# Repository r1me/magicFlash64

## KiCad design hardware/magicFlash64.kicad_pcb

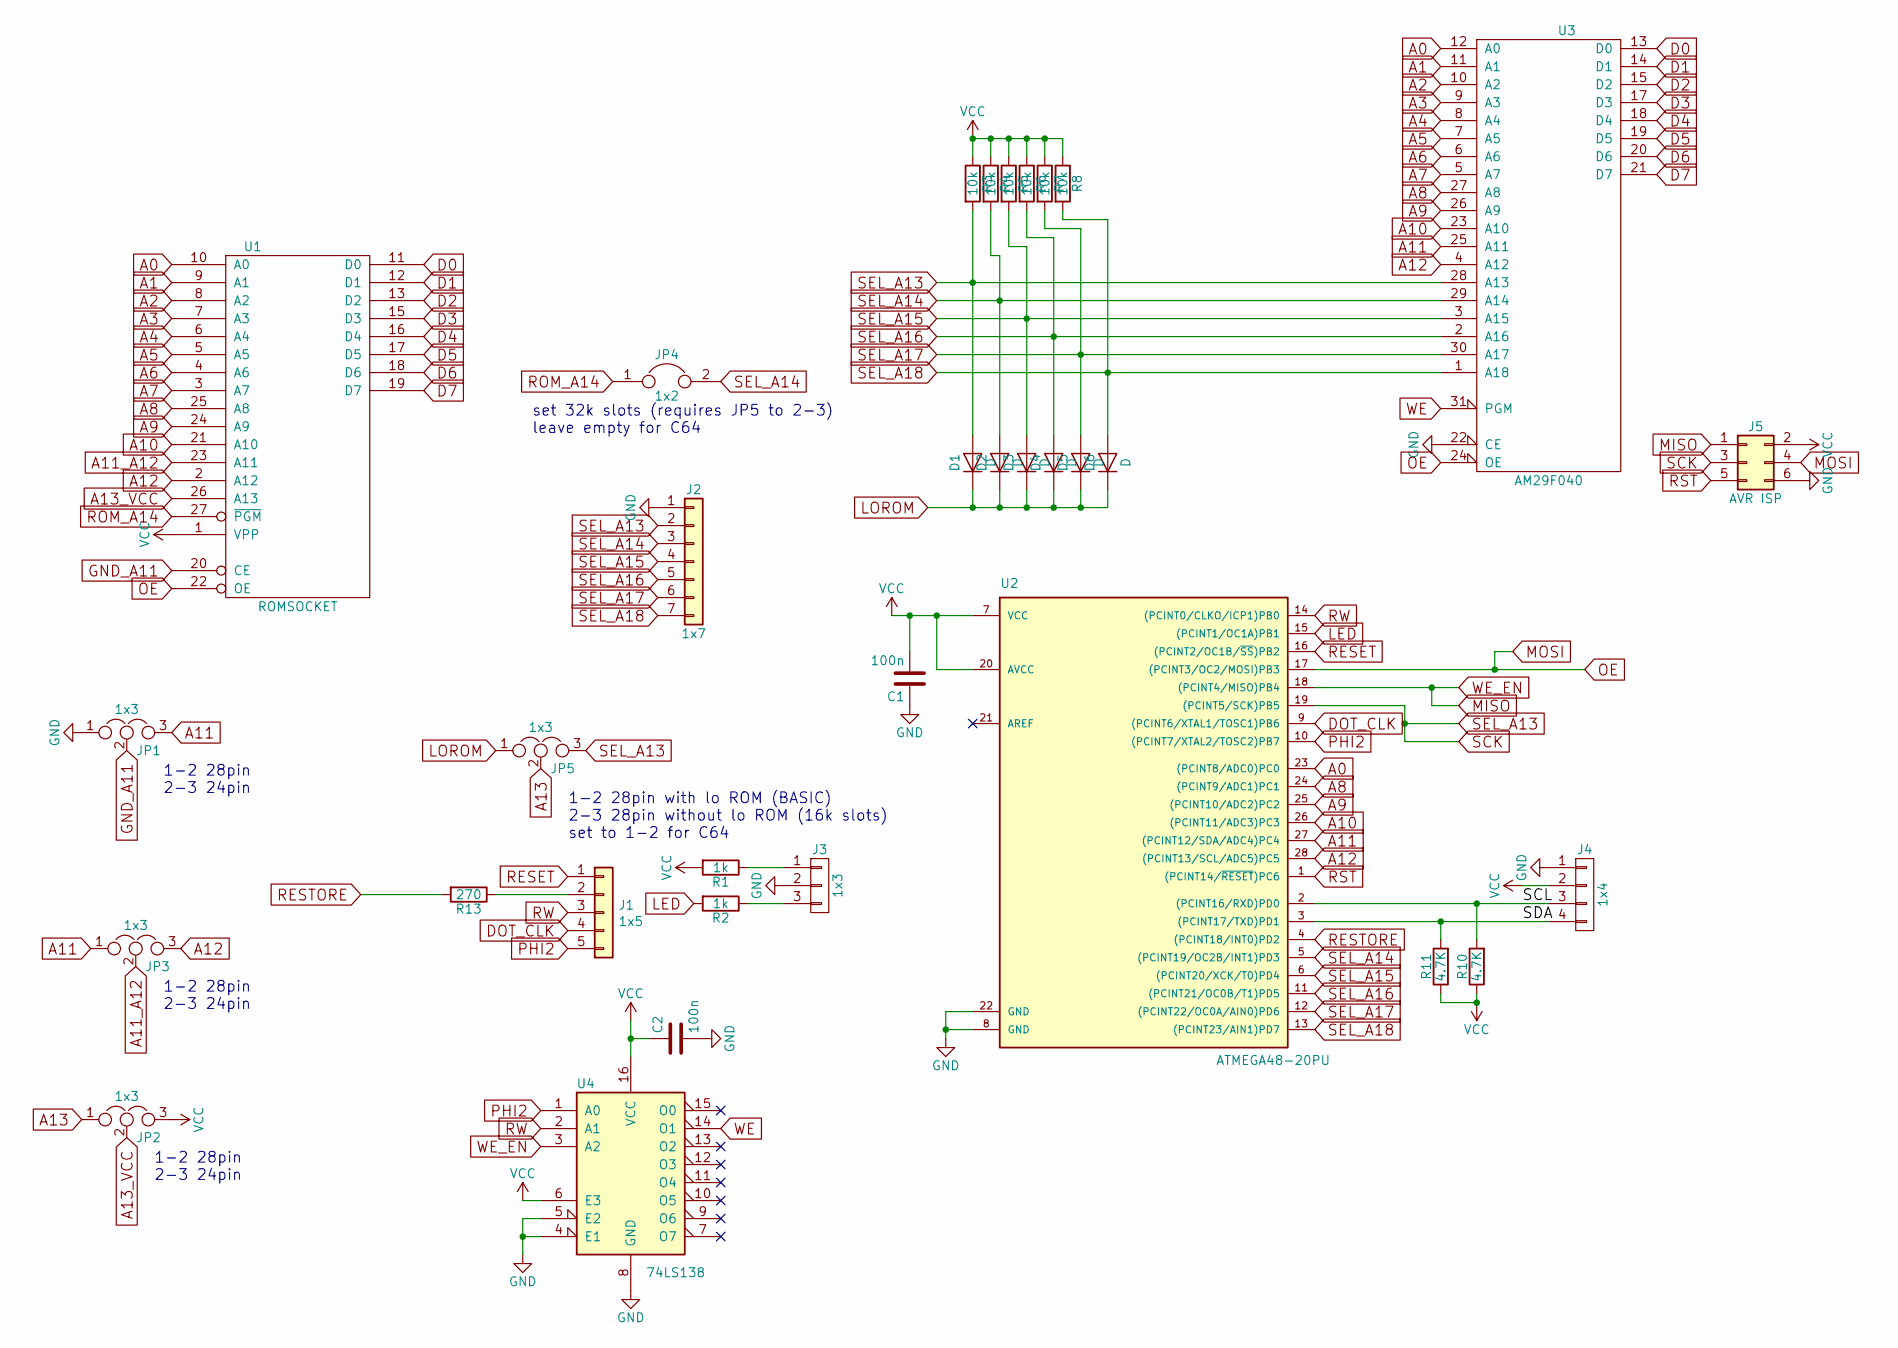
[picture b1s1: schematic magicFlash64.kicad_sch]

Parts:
C1, C2: 100n; C_1206_3216Metric
D1, D2, D3, D4, D5, D6: D; D_MiniMELF
J1: 1x5; Pin_Header_Straight_1x05_Pitch2.54mm
J2: 1x7; Pin_Header_Straight_1x07_Pitch2.54mm
J3: 1x3; Pin_Header_Straight_1x03_Pitch2.54mm
J4: 1x4; Pin_Header_Straight_1x04_Pitch2.54mm
J5: AVR ISP; Pin_Header_Straight_2x03_Pitch2.54mm
JP1, JP2, JP3, JP5: 1x3; SolderJumper-3_P1.3mm_Bridged12_RoundedPad1.0x1.5mm
JP4: 1x2; SolderJumper-2_P1.3mm_Open_RoundedPad1.0x1.5mm
R1, R2: 1k; R_1206_3216Metric
R3, R4, R5, R6, R7, R8: 10k; R_1206_3216Metric
R10, R11: 4.7K; R_1206_3216Metric
R13: 270; R_1206_3216Metric
U1: ROMSOCKET; DIP-28_W15.24mm_Socket
U2: ATMEGA48-20PU; DIP-28_W7.62mm
U3: AM29F040; PLCC32
U4: 74LS138; SO-16_3.9x9.9mm_P1.27mm

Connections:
/SCL: J4.3, R10.2, U2.2 ((PCINT16/RXD)PD0)
/SDA: J4.4, R11.2, U2.3 ((PCINT17/TXD)PD1)
A0: U1.10 (A0), U2.23 ((PCINT8/ADC0)PC0), U3.12 (A0)
A1: U1.9 (A1), U3.11 (A1)
A2: U1.8 (A2), U3.10 (A2)
A3: U1.7 (A3), U3.9 (A3)
A4: U1.6 (A4), U3.8 (A4)
A5: U1.5 (A5), U3.7 (A5)
A6: U1.4 (A6), U3.6 (A6)
A7: U1.3 (A7), U3.5 (A7)
A8: U1.25 (A8), U2.24 ((PCINT9/ADC1)PC1), U3.27 (A8)
A9: U1.24 (A9), U2.25 ((PCINT10/ADC2)PC2), U3.26 (A9)
A10: U1.21 (A10), U2.26 ((PCINT11/ADC3)PC3), U3.23 (A10)
A11: JP1.3, JP3.1, U2.27 ((PCINT12/SDA/ADC4)PC4), U3.25 (A11)
A11_A12: JP3.2, U1.23 (A11)
A12: JP3.3, U1.2 (A12), U2.28 ((PCINT13/SCL/ADC5)PC5), U3.4 (A12)
A13: JP2.1, JP5.2
A13_VCC: JP2.2, U1.26 (A13)
D0: U1.11 (D0), U3.13 (D0)
D1: U1.12 (D1), U3.14 (D1)
D2: U1.13 (D2), U3.15 (D2)
D3: U1.15 (D3), U3.17 (D3)
D4: U1.16 (D4), U3.18 (D4)
D5: U1.17 (D5), U3.19 (D5)
D6: U1.18 (D6), U3.20 (D6)
D7: U1.19 (D7), U3.21 (D7)
DOT_CLK: J1.4, U2.9 ((PCINT6/XTAL1/TOSC1)PB6)
GND: C1.1, C2.2, J2.1, J3.2, J4.1, J5.6, JP1.1, U1.14 (GND), U2.8 (GND), U2.22 (GND), U3.16 (GND), U3.22 (CE), U4.4 (E1), U4.5 (E2), U4.8 (GND)
GND_A11: JP1.2, U1.20 (CE)
LED: R2.2, U2.15 ((PCINT1/OC1A)PB1)
LOROM: D1.1 (K), D2.1 (K), D3.1 (K), D4.1 (K), D5.1 (K), D6.1 (K), JP5.1
MISO: J5.1, U2.18 ((PCINT4/MISO)PB4), U4.3 (A2)
MOSI: J5.4, U1.22 (OE), U2.17 ((PCINT3/OC2/MOSI)PB3), U3.24 (OE)
unnamed: J1.2, R13.1
unnamed: J3.1, R1.1
unnamed: J3.3, R2.1
PHI2: J1.5, U2.10 ((PCINT7/XTAL2/TOSC2)PB7), U4.1 (A0)
RESET: J1.1, U2.16 ((PCINT2/OC1B/~SS)PB2)
RESTORE: R13.2, U2.4 ((PCINT18/INT0)PD2)
ROM_A14: JP4.1, U1.27 (~PGM)
RST: J5.5, U2.1 ((PCINT14/~RESET)PC6)
RW: J1.3, U2.14 ((PCINT0/CLKO/ICP1)PB0), U4.2 (A1)
SCK: D1.2 (A), J2.2, J5.3, JP5.3, R3.2, U2.19 ((PCINT5/SCK)PB5), U3.28 (A13)
SEL_A14: D2.2 (A), J2.3, JP4.2, R4.2, U2.5 ((PCINT19/OC2B/INT1)PD3), U3.29 (A14)
SEL_A15: D3.2 (A), J2.4, R5.2, U2.6 ((PCINT20/XCK/T0)PD4), U3.3 (A15)
SEL_A16: D4.2 (A), J2.5, R6.2, U2.11 ((PCINT21/OC0B/T1)PD5), U3.2 (A16)
SEL_A17: D5.2 (A), J2.6, R7.2, U2.12 ((PCINT22/OC0A/AIN0)PD6), U3.30 (A17)
SEL_A18: D6.2 (A), J2.7, R8.2, U2.13 ((PCINT23/AIN1)PD7), U3.1 (A18)
VCC: C1.2, C2.1, J4.2, J5.2, JP2.3, R1.2, R3.1, R4.1, R5.1, R6.1, R7.1, R8.1, R10.1, R11.1, U1.1 (VPP), U1.28 (VCC), U2.7 (VCC), U2.20 (AVCC), U3.32 (VCC), U4.6 (E3), U4.16 (VCC)
WE: U3.31 (PGM), U4.14 (O1)

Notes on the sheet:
set 32k slots (requires JP5 to 2-3) leave empty for C64
1-2 28pin 2-3 24pin
1-2 28pin with lo ROM (BASIC) 2-3 28pin without lo ROM (16k slots) set to 1-2 for C64

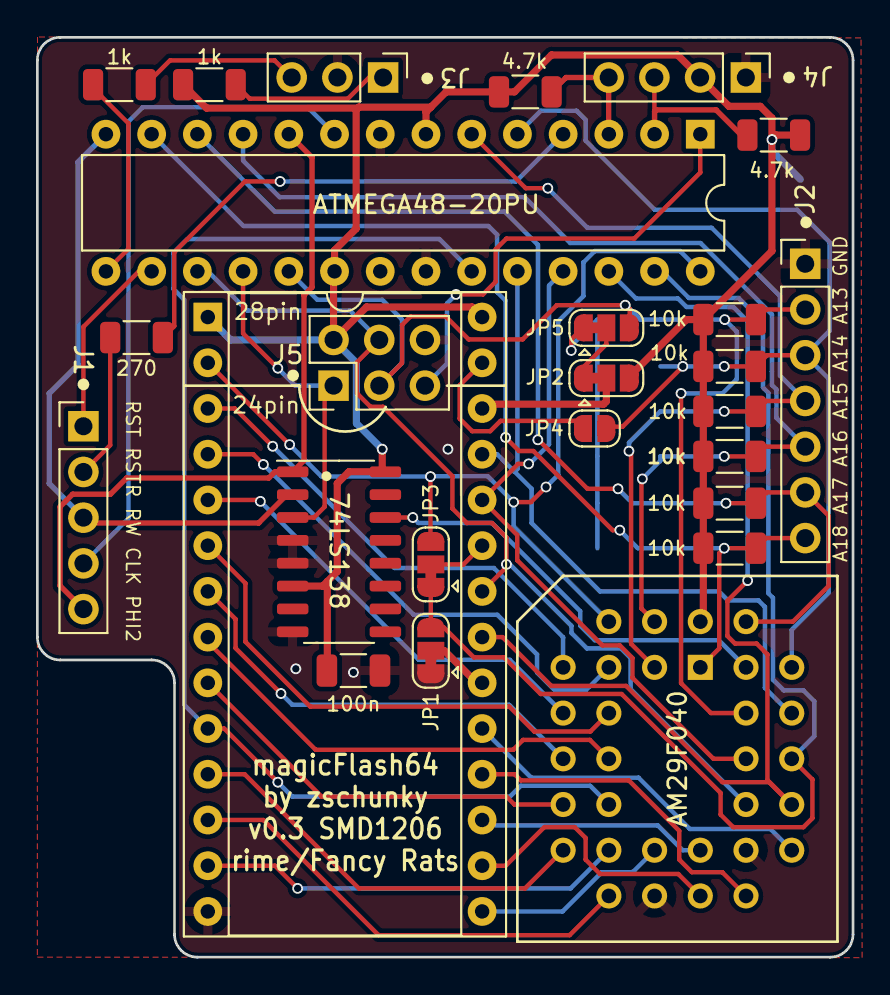
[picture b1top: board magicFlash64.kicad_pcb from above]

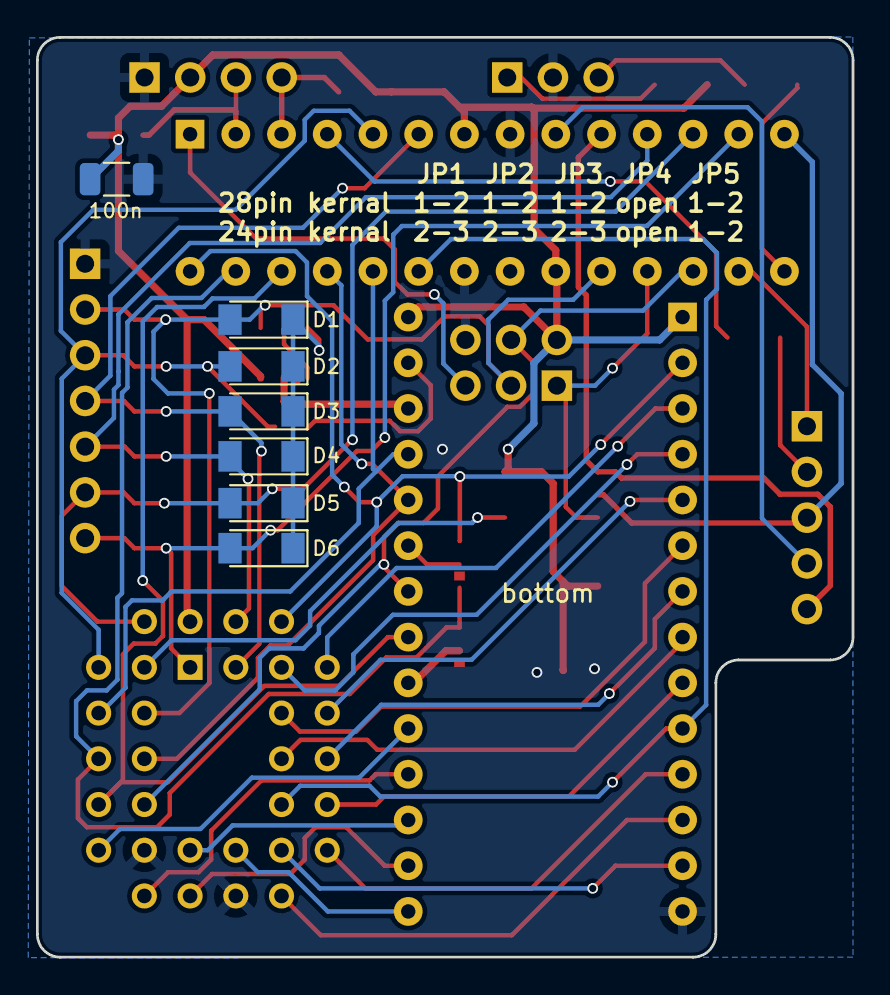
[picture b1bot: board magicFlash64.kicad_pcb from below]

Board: 2 copper layers, 45.3 x 51.1 mm, 33 parts (7 on the bottom side), 50 nets.

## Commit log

2023-08-31 Use RESTORE line as a trigger for keyman64
    A change to LOW in RESTORE line will immediately jump right into mf64 menu, so magicFlash64 can be used with keyman64 instead of RESTORE key on keyboard
2023-08-31 Set kernal to default once it's selected in menu
2023-08-31 Possible timing fix in reading default slot number from address line before writing it to EEPROM
2023-08-31 Added PCB v0.3 SMD 1206
    SMD (partially) version of v0.3 board
